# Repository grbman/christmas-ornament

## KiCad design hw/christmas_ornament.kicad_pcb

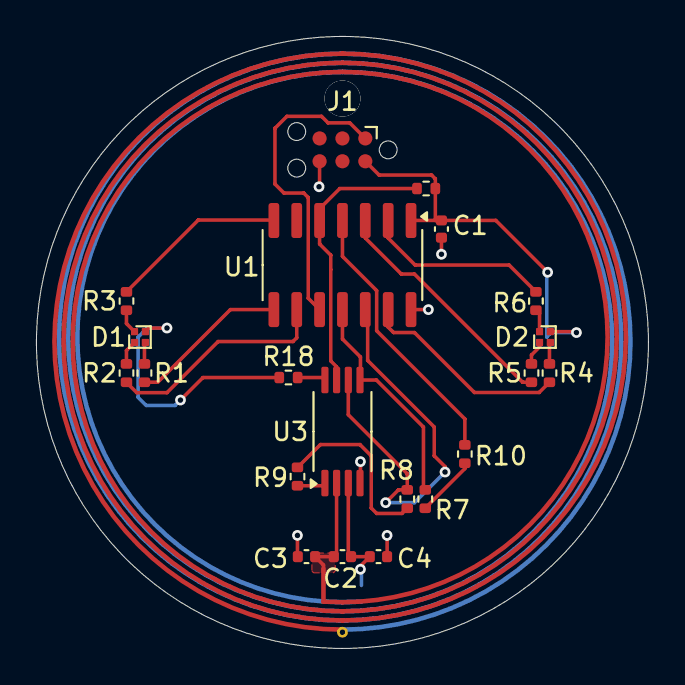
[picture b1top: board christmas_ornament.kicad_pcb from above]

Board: 2 copper layers, 34.0 x 34.0 mm, 23 parts (1 on the bottom side), 24 nets.

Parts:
AE1: Antenna_Loop; NFC_coil
BT1: Battery_Cell; BH-67D-5
C1: 0.1u; C_0402_1005Metric
C2, C3, C4: 0u; C_0402_1005Metric
D1, D2: UHD1110-FKA-CL1A13R3Q1BBQFMF3
J1: AVR-UPDI-6; Tag-Connect_TC2030-IDC-NL_2x03_P1.27mm_Vertical
R1, R4: 1.1k; R_0402_1005Metric
R2, R3, R5, R6: 100; R_0402_1005Metric
R7, R8: 20k; R_0402_1005Metric
R9, R10, R18: 0; R_0402_1005Metric
R11: 100k; R_0402_1005Metric
U1: ATtiny404-SS; SOIC-14_3.9x8.7mm_P1.27mm
U3: ST25DV04K-IER8C3; TSSOP-8_4.4x3mm_P0.65mm

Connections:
+BATT: BT1.1 (+), C1.1, D1.4 (A), D2.4 (A), J1.2 (VCC), R11.1, R18.1, U1.1 (VCC)
/I2C_SCL: R8.2, U1.12 (PA2), U3.6 (SCL)
/I2C_SDA: R7.2, U1.11 (PA1), U3.5 (SDA)
/MCU_I2C_PU: R10.1, U1.4 (PA6)
/NFC_INT: R11.2, U1.5 (PA7), U3.7 (GPO)
/UPDI: J1.1 (DATA), U1.10 (~RESET/PA0)
/V_EH: R9.1, U3.1 (V_EH)
GND: BT1.2 (-), C1.2, C3.1, C4.2, J1.6 (GND), U1.14 (GND), U3.4 (VSS)
unnamed: D1.1 (BK), R3.1
unnamed: D1.2 (GK), R2.1
unnamed: D1.3 (RK), R1.1
unnamed: D2.1 (BK), R6.1
unnamed: D2.2 (GK), R5.1
unnamed: D2.3 (RK), R4.1
unnamed: R7.1, R8.1, R9.2, R10.2
unnamed: R4.2, U1.13 (PA3)
unnamed: R6.2, U1.2 (PA4)
unnamed: R5.2, U1.3 (PA5)
unnamed: R2.2, U1.9 (PB0)
unnamed: R1.2, U1.8 (PB1)
unnamed: R3.2, U1.7 (PB2)
unnamed: AE1.1, C2.1, C3.2, U3.2 (AC0)
unnamed: AE1.2, C2.2, C4.1, U3.3 (AC1)
unnamed: R18.2, U3.8 (VCC)

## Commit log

2024-12-09 limited working NDEF text record parsing
2024-12-10 working color update over nfc
2024-12-10 working on nfc write
2024-12-10 added manual and rainbow modes
2024-12-14 more functionality
2024-12-15 code cleanup
